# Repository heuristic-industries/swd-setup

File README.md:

# Flashing STM32 Microcontrollers

What follows is the "Eric Method" for quickly and economically flashing STM32s in-circuit.
The target audience is someone new to embedded and potentially using a riff on one of our [open source firmwares](https://github.com/heuristic-industries/two-switch) in their own designs.

## Shopping list

There's a few pieces of hardware you'll need to get going; feel free to deviate if you're feeling spicy, these are just my recommendations!

- [2.54mm pitch 10 pin IDC cables](https://www.amazon.com/dp/B07FZWWGY3) (you need two cables)
- [ST-Link programmer](https://www.amazon.com/dp/B07SQV6VLZ)
- [Tag-Connect cable](https://www.tag-connect.com/product/tc2030-idc-nl)

Note that this is the 6-pin version of the Tag-Connect cable; it's convenient if you ever want to use the same cable for AVR programming as well.
The adapter board we'll talk about later maps the pinout so you can use this cable for SWD programming!

## Software Setup

### Updating the programmer

The knockoff ST-Link programmer should work out of the box, but it's a good idea to upgrade the firmware first with the official STMicro stuff.
If you find yourself doing development down the road sometimes this software can come in handy for salvaging "bricked" dev setups too.

Note: this is Windows only 😔

- Grab the [ST-Link Utility](https://www.st.com/en/development-tools/stsw-link004.html)
- Plug your programmer into your computer
- Select "Firmware update" from the "ST-LINK" drop-down menu
- Follow the instructions

### MacOS and Linux

#### Install OpenOCD

[OpenOCD](https://openocd.org/) is what we'll use to get our computer talking to the programmer.

### Windows

We'll use the St-Link Utility installed earlier to do the flashing, so there's no additional setup required.

## Hardware setup

### Adapter PCB

If you're using the no-name Amazon special programmer I linked above, you'll need an adapter board.
For reasons I will never understand, these use a non-standard SWD pinout, and can't be connected directly with a 10-pin IDC cable.

The [adapter_pcb](adapter_pcb) directory contains a full KiCad project for such an adapter board, as well as [pre-compiled gerber and assembly files](adapter_pcb/jlcpcb/production_files) that can be submitted directly to the fab of your choice (or JLCPCB if you would like it to show up assembled).

Submitting the board for fabrication and assembly is beyond the scope of this document, but something we can help with if need be!

### Your PCB

When creating PCBs to use with this setup, the KiCad library has pre-defined symbols that will make life a _lot_ easier and remove any guess-work for these pinouts.

- Production runs: `Conn_ARM_SWD_TagConnect_TC2030-NL`
- Dev boards: `Connector:Conn_ARM_JTAG_SWD_10` (use the `Connector_IDC:IDC-Header_2x05_P2.54mm_Vertical` footprint with it)

### Connecting it all

With the programmer, adapter board, and the thing you want to actually flash in hand, plug it in like so:

- Programmer plugged into computer
- "SWD (weird)" IDC cable plugged into programmer
- 6-pin connector plugged into Tag-Connect cable (for production)
  **OR**
- "SWD (normal)" plugged into the target device (for development)

## Flashing

### MacOS and Linux

#### Install OpenOCD

##### MacOS

I like [Homebrew](https://brew.sh) as a package manager.
If you have other preferences, use those, as they probably have a package for OpenOCD already.

- Install [Homebrew](https://brew.sh) (follow directions on site)
- Open a terminal and run `brew install openocd`

##### Linux

Whatever package manager you enjoy probably has a package for OpenOCD and you probably know better than I do already.
Just install it via whatever makes you happiest, or build it from source if you're feeling spicy.

#### Actually flashing it

With OpenOCD installed, we'll use the following command to do the flashing:

```sh
openocd -f interface/stlink.cfg -f target/stm32f0x.cfg -c "program PATH_TO_BINARY verify reset exit"
```

Replace `PATH_TO_BINARY` with the file path to the binary you're trying to flash.

I'm using the `stm32f0x` target here, but you may have to change the value for other processors.

### Windows

- Open the ST-Link Utility and connect your programmer and board to the computer
- Go to Target and choose "Connect"
- Select "Program & Vefify" from the Target menu
- Select the binary file to flash

## Tips and tricks

### Flashing many units

In a production run you're probably programming large batches of devices, and continually re-running the same command for each will start to get tedious.

We can use an infinite loop in your shell to continually retry programming, which allows you to press the Tag-Connect probe into each pedal and work your way down the line without having to touch the keyboard.

Press `ctrl+c` to exit the loop and interrupt the program.

```sh
for ((;;)) {
  # your programming command here
  sleep 1
}
```

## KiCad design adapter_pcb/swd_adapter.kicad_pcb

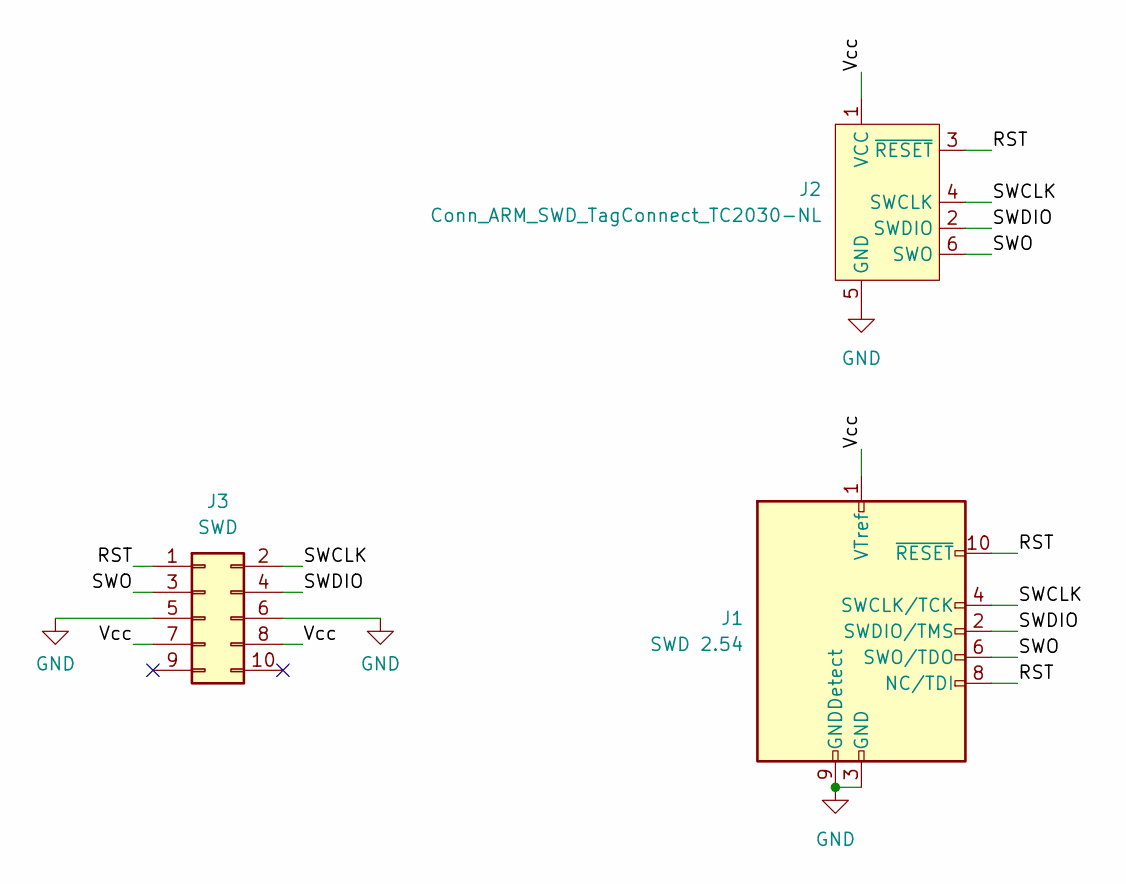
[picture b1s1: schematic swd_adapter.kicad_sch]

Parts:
J1: SWD 2.54; IDC-Header_2x05_P2.54mm_Vertical; LCSC C7501191
J2: Conn_ARM_SWD_TagConnect_TC2030-NL; IDC-Header_2x03_P2.54mm_Vertical; LCSC C11214
J3: SWD; IDC-Header_2x05_P2.54mm_Vertical; LCSC C7501191

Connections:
/RST: J1.8 (NC/TDI), J1.10 (~RESET), J2.3 (~RESET), J3.1
/SWCLK: J1.4 (SWCLK/TCK), J2.4 (SWCLK), J3.2
/SWDIO: J1.2 (SWDIO/TMS), J2.2 (SWDIO), J3.4
/SWO: J1.6 (SWO/TDO), J2.6 (SWO), J3.3
/Vcc: J1.1 (VTref), J2.1 (VCC), J3.7, J3.8
GND: J1.3 (GND), J1.5 (GND), J1.9 (GNDDetect), J2.5 (GND), J3.5, J3.6

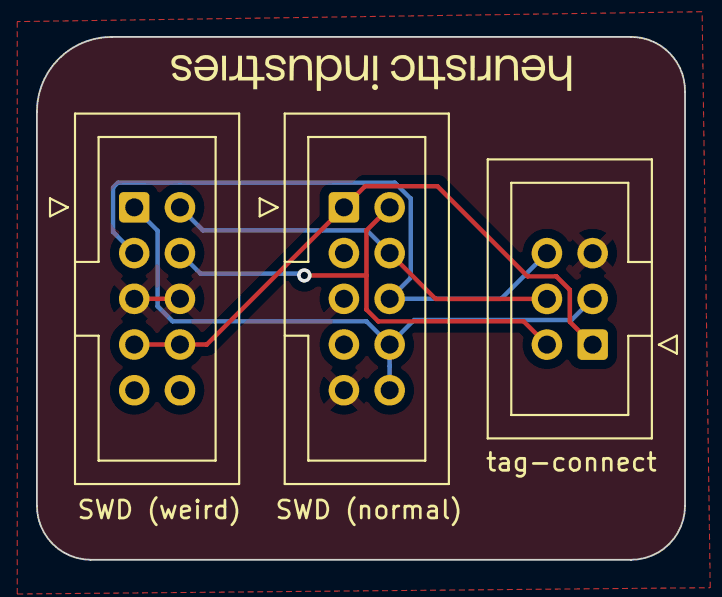
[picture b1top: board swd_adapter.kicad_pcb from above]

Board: 2 copper layers, 36.0 x 29.1 mm, 3 parts (0 on the bottom side), 6 nets.

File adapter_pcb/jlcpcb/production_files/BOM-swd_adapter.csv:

Comment,Designator,Footprint,LCSC
Conn_ARM_SWD_TagConnect_TC2030-NL,J2,IDC-Header_2x03_P2.54mm_Vertical,C11214
SWD 2.54,"J1,J3",IDC-Header_2x05_P2.54mm_Vertical,C7501191

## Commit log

2024-04-02 more stuff
